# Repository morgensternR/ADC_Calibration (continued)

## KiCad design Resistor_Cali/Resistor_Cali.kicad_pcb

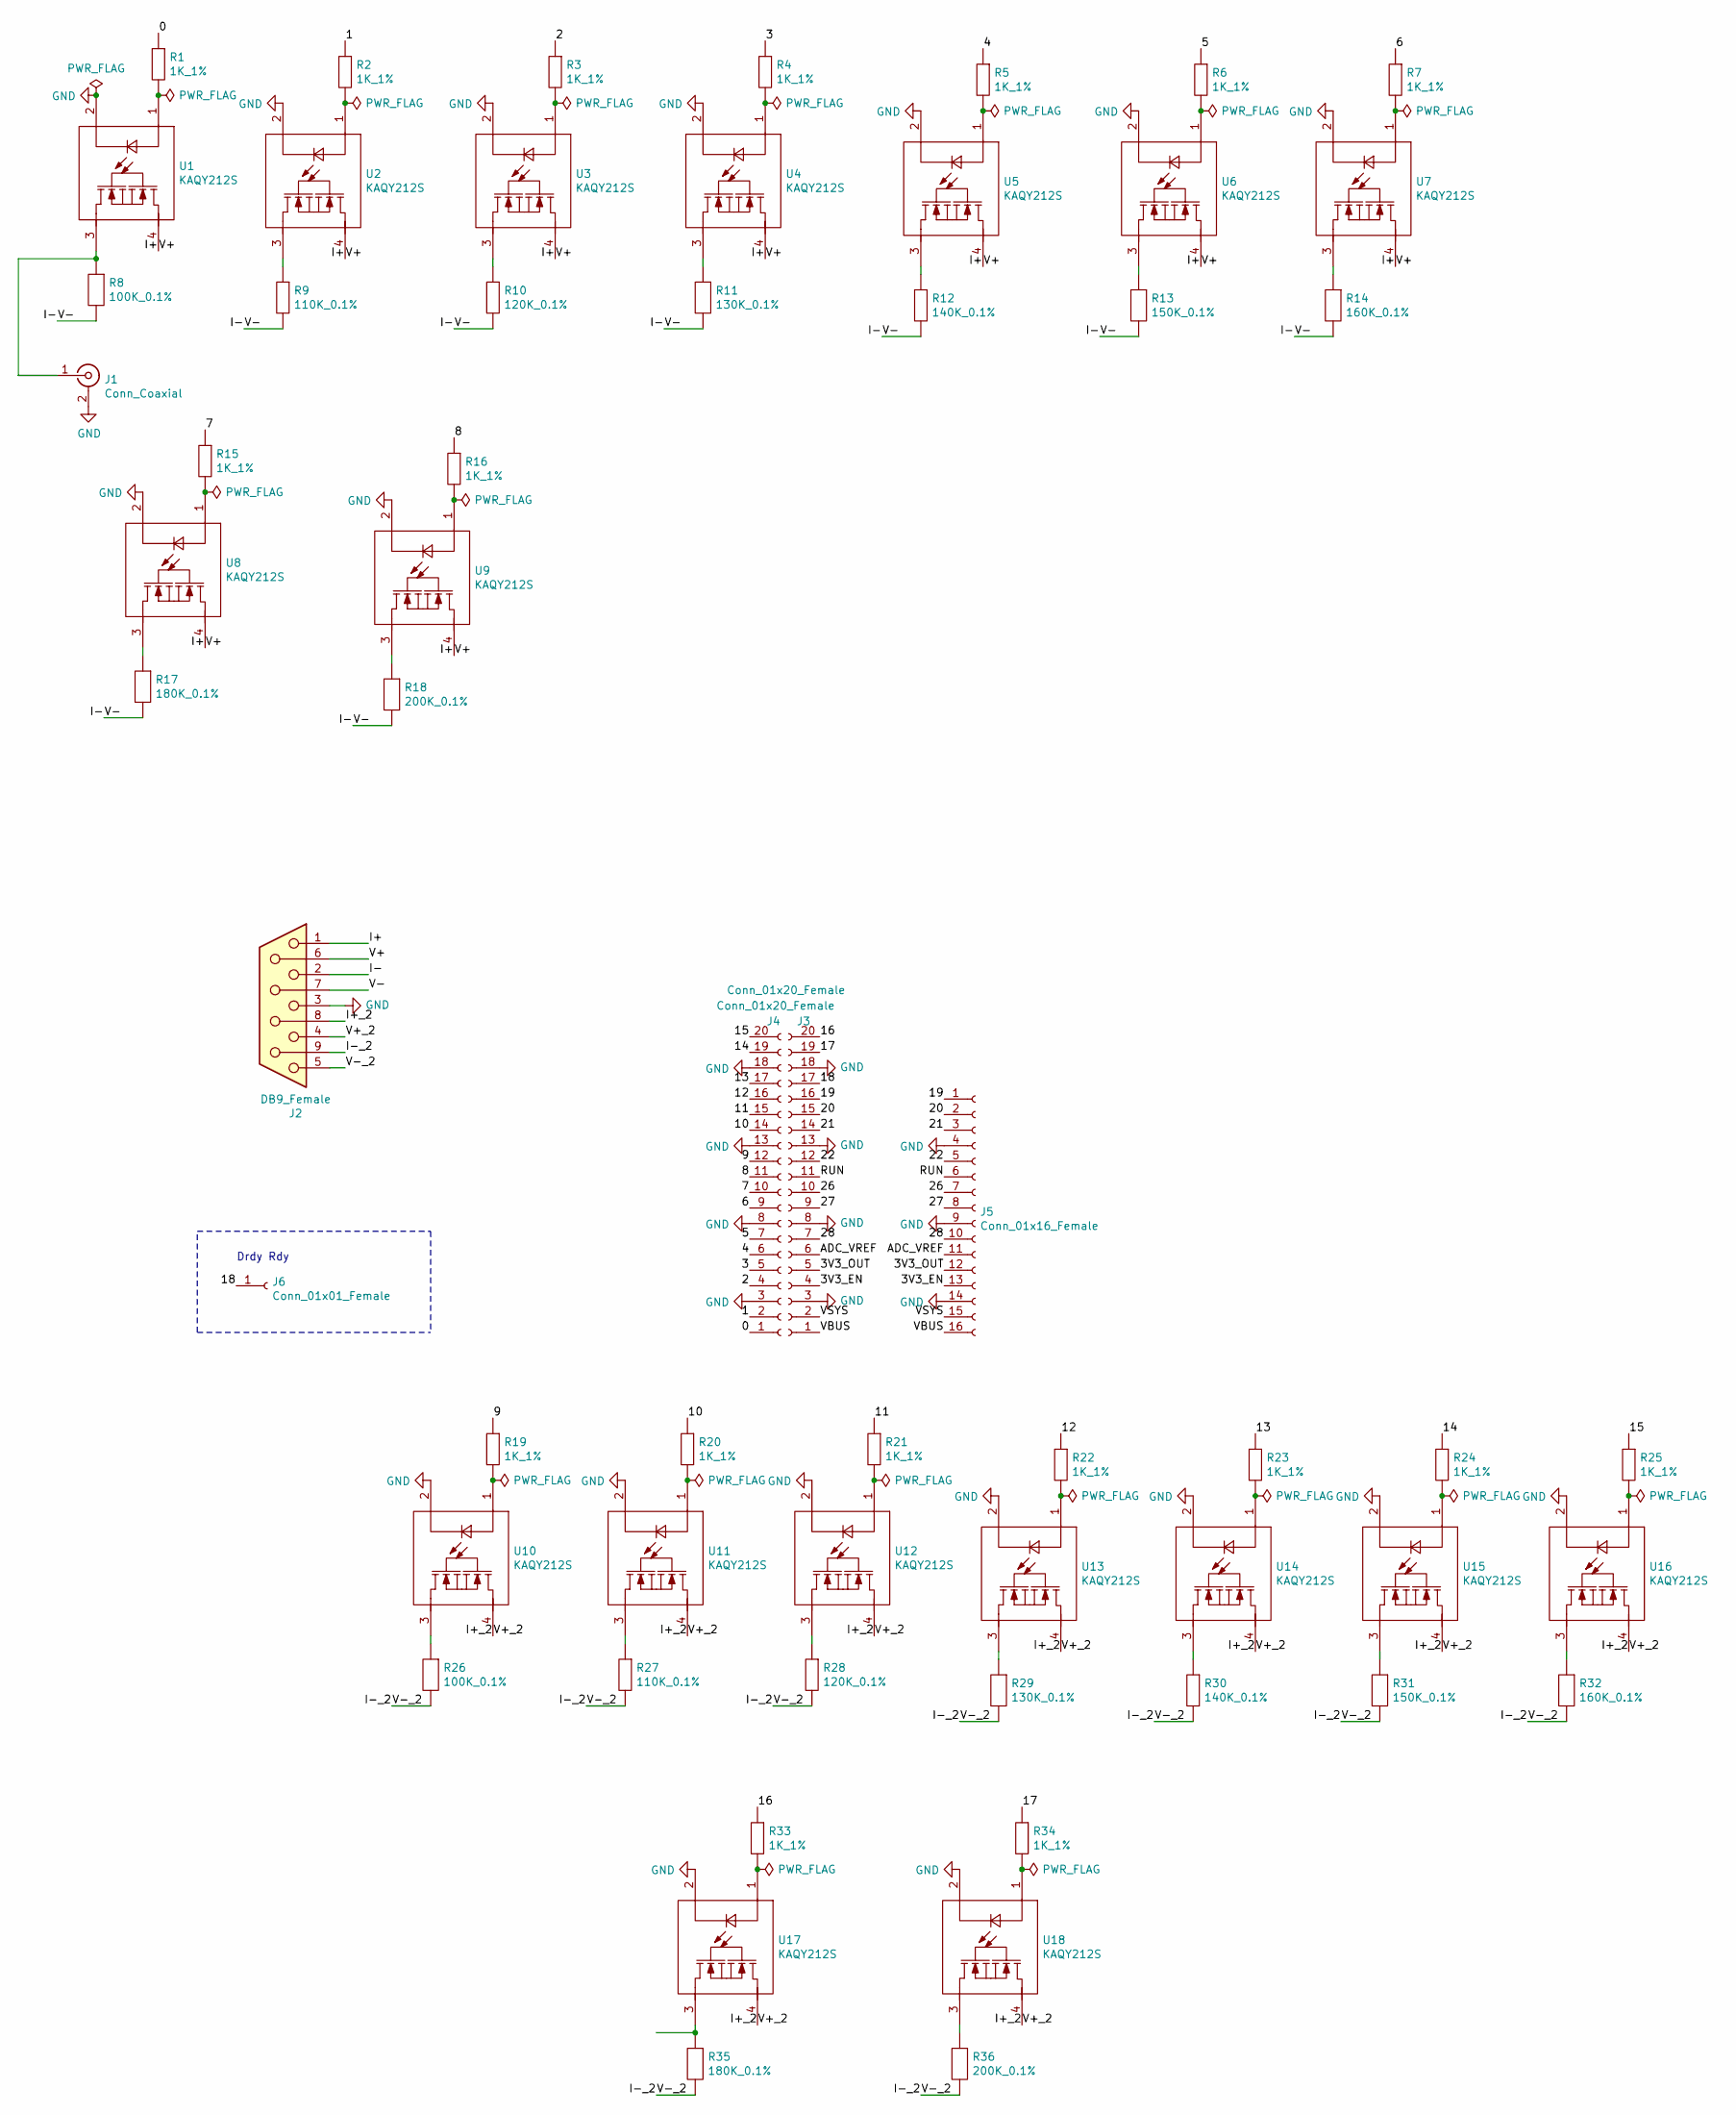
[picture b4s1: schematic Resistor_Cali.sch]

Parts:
J1: Conn_Coaxial; SMA-TH_BWSMA-KE-Z001; LCSC C496549
J2: DB9_Female; DB9_ASSMANN; LCSC C75749
J3, J4: Conn_01x20_Female; PinSocket_1x20_P2.54mm_Vertical
J5: Conn_01x16_Female; PinHeader_1x16_P2.54mm_Vertical
J6: Conn_01x01_Female; PinSocket_1x01_P2.54mm_Horizontal
R1, R2, R3, R4, R5, R6, R7, R15, R16, R19, R20, R21, R22, R23, R24, R25, R33, R34: 1K_1%; R0603; LCSC C328340
R8, R26: 100K_0.1%; R0603; LCSC C335088
R9, R27: 110K_0.1%; R0603; LCSC C326736
R10, R28: 120K_0.1%; R0603; LCSC C136959
R11, R29: 130K_0.1%; R0603; LCSC C705808
R12, R30: 140K_0.1%; R0603; LCSC C326761
R13, R31: 150K_0.1%; 150K_0.1; LCSC C413715
R14, R32: 160K_0.1%; 160K_0.1; LCSC C473318
R17, R35: 180K_0.1%; 180K_0.1; LCSC C473319
R18, R36: 200K_0.1%; R0603; LCSC C394540
U1, U2, U3, U4, U5, U6, U7, U8, U9, U10, U11, U12, U13, U14, U15, U16, U17, U18: KAQY212S; SOP-4_L4.4-W4.0-P2.54-LS7.0-BL; LCSC C194898

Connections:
/0: J3.1, R1.1
/1: J3.2, R2.1
/2: J3.4, R3.1
/3: J3.5, R4.1
/3V3_EN: J4.4, J5.13
/3V3_OUT: J4.5, J5.12
/4: J3.6, R5.1
/5: J3.7, R6.1
/6: J3.9, R7.1
/7: J3.10, R15.1
/8: J3.11, R16.1
/9: J3.12, R19.1
/10: J3.14, R20.1
/11: J3.15, R21.1
/12: J3.16, R22.1
/13: J3.17, R23.1
/14: J3.19, R24.1
/15: J3.20, R25.1
/16: J4.20, R33.1
/17: J4.19, R34.1
/18: J4.17, J6.1
/19: J4.16, J5.1
/20: J4.15, J5.2
/21: J4.14, J5.3
/22: J4.12, J5.5
/26: J4.10, J5.7
/27: J4.9, J5.8
/28: J4.7, J5.10
/ADC_VREF: J4.6, J5.11
/I+: J2.1, J2.6, U1.4, U2.4, U3.4, U4.4, U5.4, U6.4, U7.4, U8.4, U9.4
/I+_2: J2.4, J2.8, U10.4, U11.4, U12.4, U13.4, U14.4, U15.4, U16.4, U17.4, U18.4
/I-: J2.2, J2.7, R8.2, R9.2, R10.2, R11.2, R12.2, R13.2, R14.2, R17.2, R18.2
/I-_2: J2.5, J2.9, R26.2, R27.2, R28.2, R29.2, R30.2, R31.2, R32.2, R35.2, R36.2
/RUN: J4.11, J5.6
/VBUS: J4.1, J5.16
/VSYS: J4.2, J5.15
GND: J1.2 (Ext), J2.0, J2.3, J3.3, J3.8, J3.13, J3.18, J4.3, J4.8, J4.13, J4.18, J5.4, J5.9, J5.14, U1.2, U2.2, U3.2, U4.2, U5.2, U6.2, U7.2, U8.2, U9.2, U10.2, U11.2, U12.2, U13.2, U14.2, U15.2, U16.2, U17.2, U18.2
unnamed: J1.1 (In), R8.1, U1.3
unnamed: R1.2, U1.1
unnamed: R2.2, U2.1
unnamed: R3.2, U3.1
unnamed: R4.2, U4.1
unnamed: R5.2, U5.1
unnamed: R6.2, U6.1
unnamed: R7.2, U7.1
unnamed: R9.1, U2.3
unnamed: R10.1, U3.3
unnamed: R11.1, U4.3
unnamed: R12.1, U5.3
unnamed: R13.1, U6.3
unnamed: R14.1, U7.3
unnamed: R15.2, U8.1
unnamed: R16.2, U9.1
unnamed: R17.1, U8.3
unnamed: R18.1, U9.3
unnamed: R19.2, U10.1
unnamed: R20.2, U11.1
unnamed: R21.2, U12.1
unnamed: R22.2, U13.1
unnamed: R23.2, U14.1
unnamed: R24.2, U15.1
unnamed: R25.2, U16.1
unnamed: R26.1, U10.3
unnamed: R27.1, U11.3
unnamed: R28.1, U12.3
unnamed: R29.1, U13.3
unnamed: R30.1, U14.3
unnamed: R31.1, U15.3
unnamed: R32.1, U16.3
unnamed: R33.2, U17.1
unnamed: R34.2, U18.1
unnamed: R35.1, U17.3
unnamed: R36.1, U18.3

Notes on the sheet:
Drdy Rdy

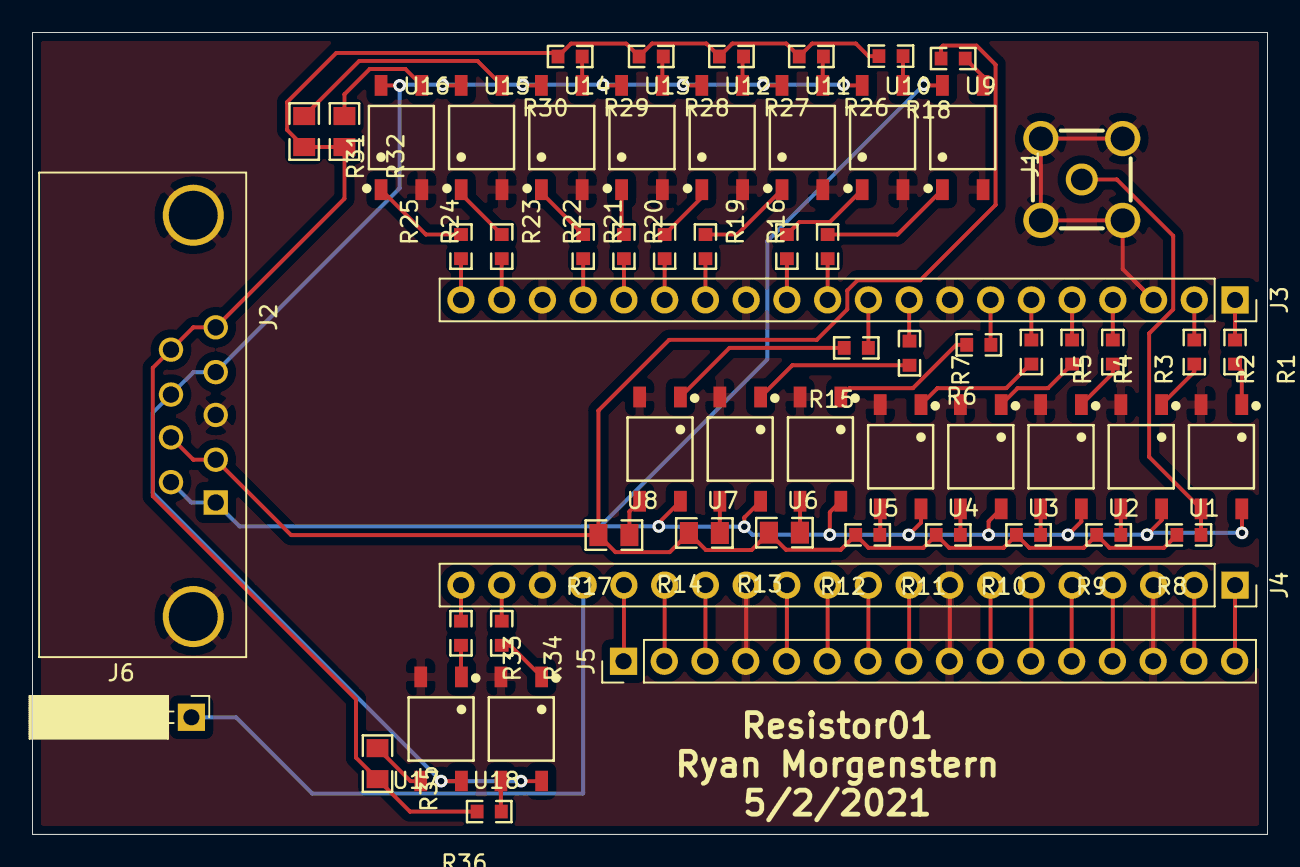
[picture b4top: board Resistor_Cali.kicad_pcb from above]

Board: 2 copper layers, 77.0 x 50.0 mm, 60 parts (0 on the bottom side), 73 nets.

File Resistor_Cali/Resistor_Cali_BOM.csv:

"Id";"Designator";"Package";"Quantity";"Designation";"Supplier and ref";
1;"J1";"SMA-TH_BWSMA-KE-Z001";1;"Conn_Coaxial";;;
2;"U16,U15,U7,U14,U6,U13,U18,U5,U12,U4,U17,U11,U3,U10,U9,U2,U8,U1";"SOP-4_L4.4-W4.0-P2.54-LS7.0-BL";18;"KAQY212S";;;
3;"R25,R24,R7,R23,R6,R22,R34,R5,R21,R4,R33,R20,R3,R19,R16,R2,R15,R1";"R0603";18;"1K_1%";;;
4;"R32,R14";"160K_0.1";2;"160K_0.1%";;;
5;"R31,R13";"150K_0.1";2;"150K_0.1%";;;
6;"R30,R12";"R0603";2;"140K_0.1%";;;
7;"R29,R11";"R0603";2;"130K_0.1%";;;
8;"R36,R18";"R0603";2;"200K_0.1%";;;
9;"R28,R10";"R0603";2;"120K_0.1%";;;
10;"R35,R17";"180K_0.1";2;"180K_0.1%";;;
11;"R27,R9";"R0603";2;"110K_0.1%";;;
12;"R26,R8";"R0603";2;"100K_0.1%";;;
13;"J5";"PinHeader_1x16_P2.54mm_Vertical";1;"Conn_01x16_Female";;;
14;"J4,J3";"PinSocket_1x20_P2.54mm_Vertical";2;"Conn_01x20_Female";;;
15;"J2";"DB9_ASSMANN";1;"DB9_Female";;;
16;"J6";"PinSocket_1x01_P2.54mm_Horizontal";1;"Conn_01x01_Female";;;

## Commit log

2022-04-19 Initial
2022-05-05 New Design
2022-05-10 Upddate
2022-05-11 Update
    Nearly finished versions of simple and Calibrator board
2022-05-12 Removed resistor_02 bc bad name
2022-05-12 Fixed jst pinouts and made Cali board
2022-05-17 Added Resistors to Diodes
2022-05-18 Fixed footprint
2022-05-18 Fixed PCB Name
2022-05-18 Moved old files
2022-05-20 Fixed trace distance
2022-08-09 added code
2023-01-26 can read adc without sleep
2023-01-26 added gain
2023-01-26 Updated readme and some code
2023-06-21 Create LICENSE
